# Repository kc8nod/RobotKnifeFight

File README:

Robot Knife Fight v0.10 (master)

Robot Knife Fight is a game that uses Python 2.7+, Arduino v1.0.3+, OpenCV 2.4.5+, and zbar 0.10 to scan a video source for QR codes for robot positions, if the robot is alive, and the arena's edges.  The position is sent out via an Arduino transmitter using a Virtual Wire 433Mhz Radio to each Arduino robot.  Each robot has a balloon covering it's DEAD symbol that also holds down it's power button.  When it's balloon pops the robot turns off.

The game is simple.  Each robot tries to pop the balloon of the other robots and be the last alive.

We are currently in Beta stages.  Positioning works but could use some optimizations.  The 433Mhz Radio that each Arduino uses to receive the position of itself and the other robots could use review.  The QR scanning with zbar could be set to focus on just the arena area.  Setting zbar to increase the number of scanning passes on certain areas of the image is also possible.

3d_model/                           #Sketchup design files for the robot.
code/arena/                         #Python script that scans the video for QR codes
                                    # and sends commands to the transmitter.
code/example_bot_attack /           #Arduino robot code that drives straight towards
                                    # the nearest living robot.
code/example_bot_patrol/            #Arduino robot code patrols between 4 points.
code/libraries/                     #Libraries you will need to copy to your 
                                    # 'arduino/libraries' folder.
code/rkf_xmit/                      #Arduino code for the transmitter.
code/serial_drivable_bot/           #Arduino robot code that's drivable via serial
                                    # commands (Xbee, Bluetooth, etc.)
code/serial_keyboard_controller/    #Processing script to drive up to 2 bots via
                                    # serial connections.
harware/                            #Shield Schematic for Virtual Wire Radio, servo
                                    # connectors, switch connectors, and a serial
                                    # module (Bluetooth Mate, FTDI pinout).
lasercut/                           #The exported DXF file of the Flat_Pack.skp for
                                    # lasercutting the robot.
qrcodes/                            #PNG files of the QR codes for the arena corners
                                    # (A###-C#), Robot symbols (http://###), and the
                                    # robot death symbols (DEAD###).

We currently suggest print sizes of 5.25"x5.25" for arena corners and 4.25"x4.25" for robot symbols.

Check http://i3detroit.com for events.

https://github.com/SWiT/RobotKnifeFight
https://github.com/kc8nod/RobotKnifeFight

https://github.com/SWiT/RobotFightClubArena

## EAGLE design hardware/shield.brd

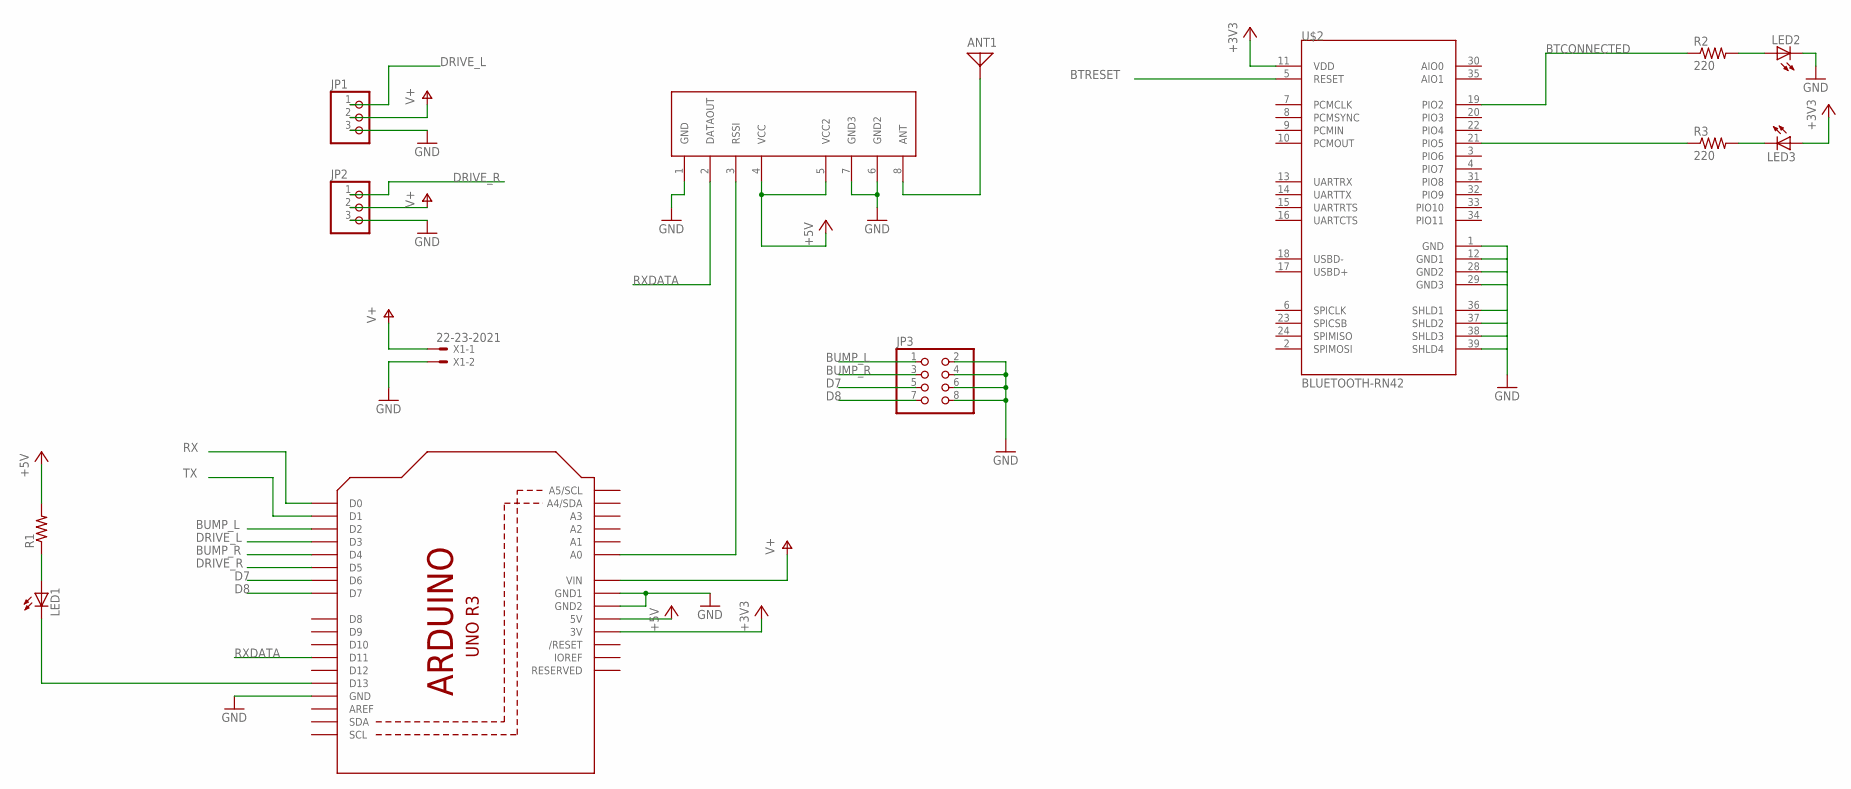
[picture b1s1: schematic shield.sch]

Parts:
ANT1: ANTENNA; PAD-01
JP1, JP2: PINHD-1X3; 1X03
JP3: PINHD-2X4; 2X04
LED1, LED2, LED3: LED3MM
R1: R-US_R0805; R0805
R2, R3: 220; R0805
U1: ARDUINOR3-DIMENSION; ARDUINOR3
U$1: RWS371; RWS-371
U$2: BLUETOOTH-RN42; RN42
X1: 22-23-2021

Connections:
+3V3: LED3.A, U1.3V, U$2.11 (VDD)
+5V: R1.2, U1.5V, U$1.4 (VCC), U$1.5 (VCC2)
BTCONNECTED: R2.1, U$2.19 (PIO2)
BTRESET: U$2.5 (RESET)
BUMP_L: JP3.1, U1.D2
BUMP_R: JP3.3, U1.D4
D7: JP3.5, U1.D6
D8: JP3.7, U1.D7
DRIVE_L: JP1.1, U1.D3
DRIVE_R: JP2.1, U1.D5
GND: JP1.3, JP2.3, JP3.2, JP3.4, JP3.6, JP3.8, LED2.K (C), U1.GND, U1.GND1, U1.GND2, U$1.1 (GND), U$1.6 (GND2), U$1.7 (GND3), U$2.1 (GND), U$2.12 (GND1), U$2.28 (GND2), U$2.29 (GND3), U$2.36 (SHLD1), U$2.37 (SHLD2), U$2.38 (SHLD3), U$2.39 (SHLD4), X1.2
unnamed: U1.A0, U$1.3 (RSSI)
unnamed: LED1.A, R1.1
unnamed: LED1.K (C), U1.D13
unnamed: ANT1.1, U$1.8 (ANT)
unnamed: LED2.A, R2.2
unnamed: LED3.K (C), R3.2
unnamed: R3.1, U$2.21 (PIO5)
RX: U1.D0
RXDATA: U1.D11, U$1.2 (DATAOUT)
TX: U1.D1
V+: JP1.2, JP2.2, U1.VIN, X1.1

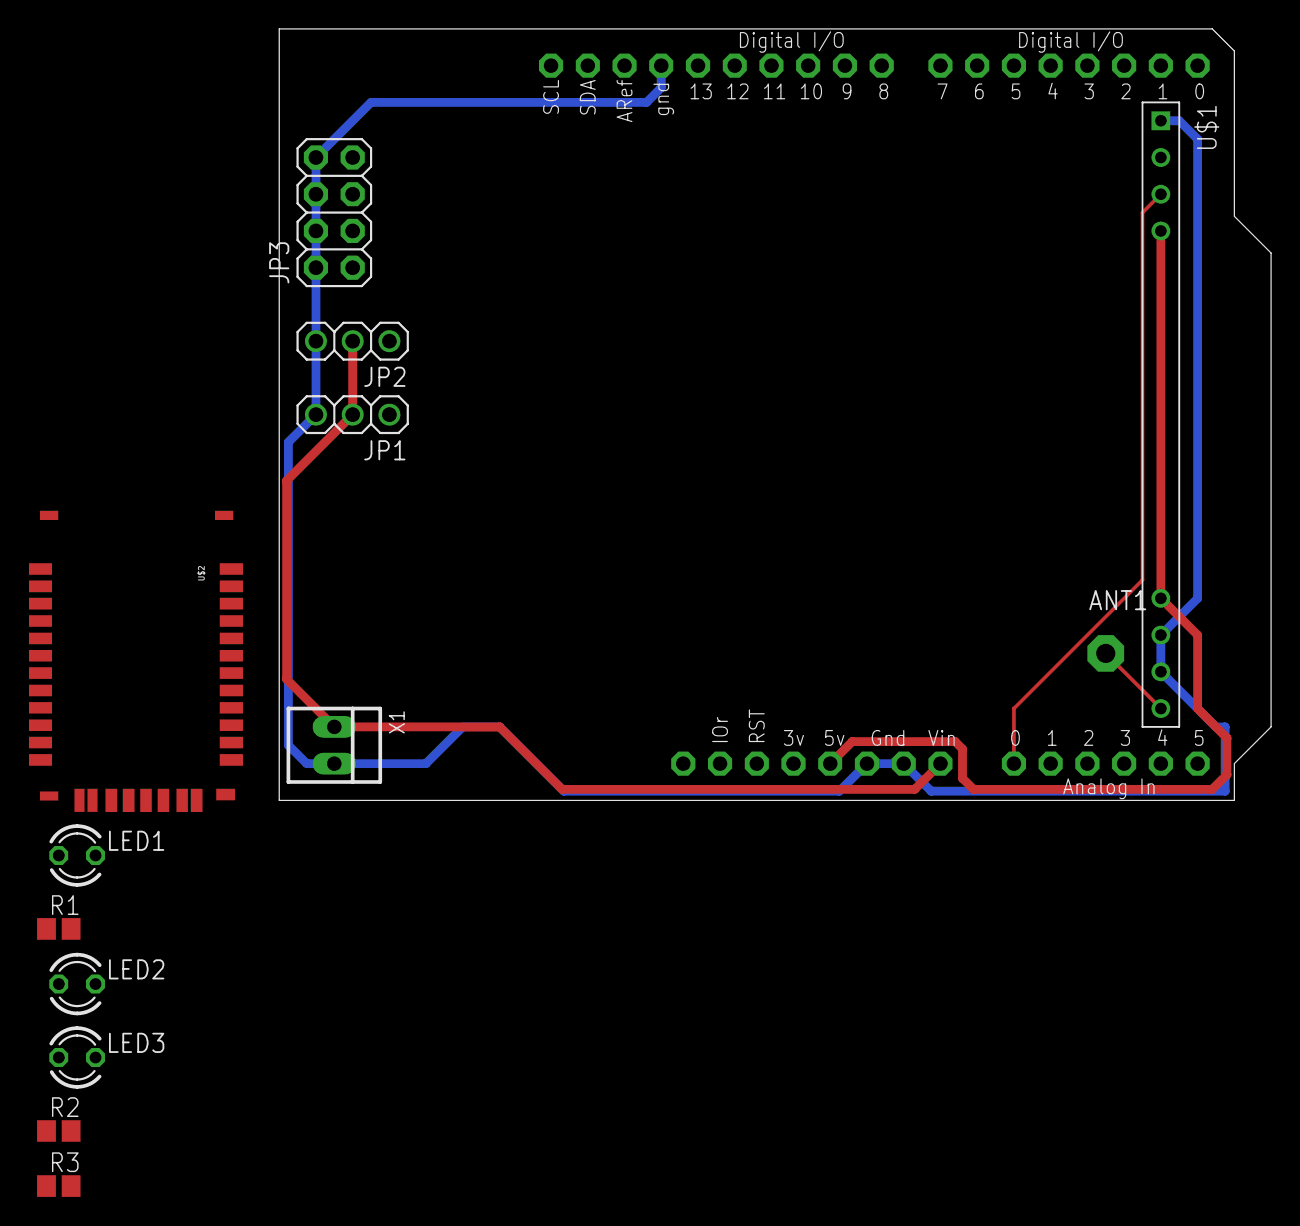
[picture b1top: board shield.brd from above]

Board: 2 copper layers, 68.6 x 53.3 mm, 14 parts (0 on the bottom side), 19 nets.

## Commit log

2012-02-14 add v1.3 files
2012-02-14 shuffle files
2012-02-15 create rx test code
2012-03-04 add detroit_test and opecvtest
2012-03-06 updated sketchup models. added new bottom plate to lasercut dxf
2012-03-06 added bumpers to lasercut dxf. crown is missing.
2012-03-29 narrowed up the vertical bits. re-kajiggered the bumpers to be smaller and overlap the bottom plate.
2012-04-01 Added feature detect function and simple test script
2012-04-01 Group points from feature detect to identify likely objects
2012-04-01 Made test script more cross-platform
2012-04-02 lower profile bumper. narrower vertical members.
2012-04-02 add some docs
2012-04-02 bumpers, verticals and crown all back in
2012-04-02 add registration holes
2012-04-02 square up orientation
2012-04-24 add rf test examples.
2012-05-02 add rc bot and keyboard control
2012-05-02 remove obsolete stuff
2012-05-08 fixed transmit initialization
2012-05-08 fix range of speed commands
2012-05-11 working rc_bot example
2012-05-11 document the transmitter interface
2012-06-03 add serialcommand library
2012-06-04 Added pyTUIO library (snapshot from 11/5/2008)
2012-06-05 Simple script to send robot positions to transmitter.
2012-06-05 move the transmitter doc. fix the id in send_pos.py
2012-06-18 started calibration for arena
2012-07-10 fixed syntax error
2012-07-10 optimized radio settings and code for bot and transmitter. Redefined pins and servo values for latest bot design.
2012-07-12 create camera calibration script. still needs debugging
2012-07-14 started example bot code that will accept test commands over Serial and position data of over the radio
2012-07-14 added some commands to drive over the BT serial radio.
2012-07-15 example bot code that is drivable over the main Serial connection at 57600bps. bot will stop and backup a little if a bumpswitch is triggered.
2012-07-16 move some functions to seperate files. BT Serial debugging works but a 115200bps baud is required
2012-07-17 fixed the camera -> arena transform and calibration script
2012-07-17 forgot to read config in send_pos and camera_test
2012-07-18 fixed calibrate almost...
2012-07-23 help menu rendered with out a /r in putty
2012-07-24 allow debug command submission by \n AND \r. improved default xmit period.
2012-07-26 updated arena size defaults
2012-07-26 send_pos.py works now
2012-07-26 started rkf_game.py file for coordinating the start of the game, logging kills etc.
2012-07-26 almost there, some numbers are going negative when converting from camera to arena
2012-07-27 fixed calibrate.py defaults. attempting to fix coordinates
2012-08-02 added bumper_test_bot, non-position aware AI. some python code from Maker Faire.
2012-08-02 bumper_test_bot
2012-08-02 better servo timing, serial baud compatible with BT Mate
2012-08-03 fixed bot thought process, better comments reset stop position to 1500ms for ServoTimer2 removed setup blink
2012-08-09 prompting
2012-08-09 better
2012-08-09 better default camer resolution of 720p
2012-08-10 fixing calibration, not done yet
2012-08-12 calibate now asks for camera resolution
2012-08-23 updated id pairings
2012-08-25 testing reactivision delay from waiting for input
2012-09-17 Arduino local echo serial test scipt, Processing keyboard controller.
2012-09-17 almost BT drivable
2012-09-17 reactivision testing and examplebot breakage
2012-09-18 BT DRIVABLE!!!!!
2012-09-18 improving steering. starting to anyways.
2012-09-20 better but not done.
2012-09-20 vastly improved steering
2012-09-20 Now with speed control
2012-09-20 throttle works.
2012-09-23 serial port is now selectable.
2012-09-23 improved drawing functions, improved keyCode defining.
2012-09-23 starting to create Player Class.
2012-09-23 moved to a player object model. 1-4 Players possible.
2012-09-23 Draws Keys on top of buttons. removed boxSize variable, no need to scale interface. Simplified positioning math. Updated wiimote script
2012-10-01 poll the update function to get latest position data
2012-10-06 JSON format serial data.
2012-10-06 removed extra holes. tweaked ballon key hole and tab length on crown. flatted rest on side for symbol plate. added arm, symbol plate, and bump guard.
2012-10-06 fixed symbol plate. removed excess/old files
2012-10-06 Assembled bot,fixed bump guard.
2012-10-18 tabs connecting symbol plate and sides. Flat Pack
2013-02-25 create shield schematic. partial layout.
2013-04-09 add .stl file to try out the github renderer
2013-04-18 added gitignore
2013-04-21 beginning QR code based arena
2013-04-22 finally figured out how to focus the camera
2013-04-26 multi qr code positions works! field of view needs improvement
2013-05-03 QR Codes
2013-05-28 working with OpenCV 2.4.5
2013-05-28 recognizes DEAD symbols.
2013-05-29 better readability
2013-05-30 bot heading
2013-06-01 resolution selection, data only dosplay mode
2013-06-02 bot view, example drive command, removed pytuio
2013-06-02 change color when dead, output status when bumper triggered
2013-06-03 arena location, reset arena, toggle bot dead/alive, draw statuses
2013-06-03 typo fix
2013-06-03 starting to use arduino transmitter
2013-06-03 removed old files
2013-06-04 transmitting, upped transmitter baud
2013-06-05 example bot navigate to destination point. arena ready.
2013-06-06 trying to improve radio performance.
2013-06-06 example bot can hold a heading now!!!
2013-06-07 overlay on color image. turn amount based on distance. stop function. new output statuses.
2013-06-07 patrolling poorly, but it does work.
2013-06-07 better patrolling, but slower.
2013-06-08 better patrolling, still not great
2013-06-08 renamed example_bot example_bot_patrol, started example_bot_attack
2013-06-08 attack bot!
2013-06-09 attack bot bugfix
2013-06-09 starting runaway bot
2013-06-09 runaway bot
2013-06-09 patrol_bot does a better job of staying alive than runaway_bot
2013-06-10 renamed bt_ bot files to serial_ bot files. updated README.
2013-06-13 origin moved some bot code works, other bots broken
2013-06-29 add bluetoothdevice to schematic
2013-06-29 for the transmitter: added the alive flag to the position changed the overall packet size to 13 bytes packet header is only one byte.
2013-06-29 improved attack bot, arena position buggy after switch to Quadrant I notation
2013-06-29 valid becomes alive, added fresh
2013-06-29 moved rfc_qr_arena.py for conveinence. removed runaway bot since it didn't work.
2013-06-29 fixed patrol bot
2013-06-30 moving to 64 possible headings
2013-06-30 patrol bot now supports 64 possible headings
